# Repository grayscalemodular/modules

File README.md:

Technical documentation and source files for synthesizer modules developed by [Grayscale](https://grayscale.info/)

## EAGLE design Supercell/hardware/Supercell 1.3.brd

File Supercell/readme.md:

Supercell
=======

[Supercell](https://grayscale.info/supercell/) is a Eurorack synthesizer module from [Grayscale](https://grayscale.info/). It is primarily based on [Clouds](https://mutable-instruments.net/modules/clouds/) by [Mutable Instruments](https://mutable-instruments.net/). The original source files for Clouds can be found in the Mutable Instruments [Github](https://github.com/pichenettes/eurorack) repository.

Visit [grayscale.info/supercell/](https://grayscale.info/supercell/) for more information.

Hardware
=======

The schematic and PCB files for this project are distributed under the Creative Commons [CC-BY-SA 3.0](https://creativecommons.org/licenses/by-sa/3.0/) license, the same license used by the Clouds source files.

CC BY-SA license terms do not confer the right to use intellectual property such as trademarks, brand names, and logos. Grayscale, Microcell, Mutable Instruments, and Clouds are trademarks of their respective owners and should not be used without permission.

Firmware
=======

Supercell supports the Superparasites firmware, which combines elements of the original Clouds DSP code by [Mutable Instruments](https://github.com/pichenettes/eurorack), the [Parasites](https://mqtthiqs.github.io/parasites/clouds.html) alternate firmware by Matthias Puech, and the [Beat Repeat](https://github.com/jkammerl/eurorack) alternate firmware by Julius Kammerl. All source code is available on the [GitHub repo](https://github.com/patrickdowling/superparasites) maintained by Patrick Dowling. Thanks to all involved for their work on this hybrid code base.

Source code for this project is distributed under the MIT License. See [github.com/patrickdowling/superparasites](https://github.com/patrickdowling/superparasites) for source code.

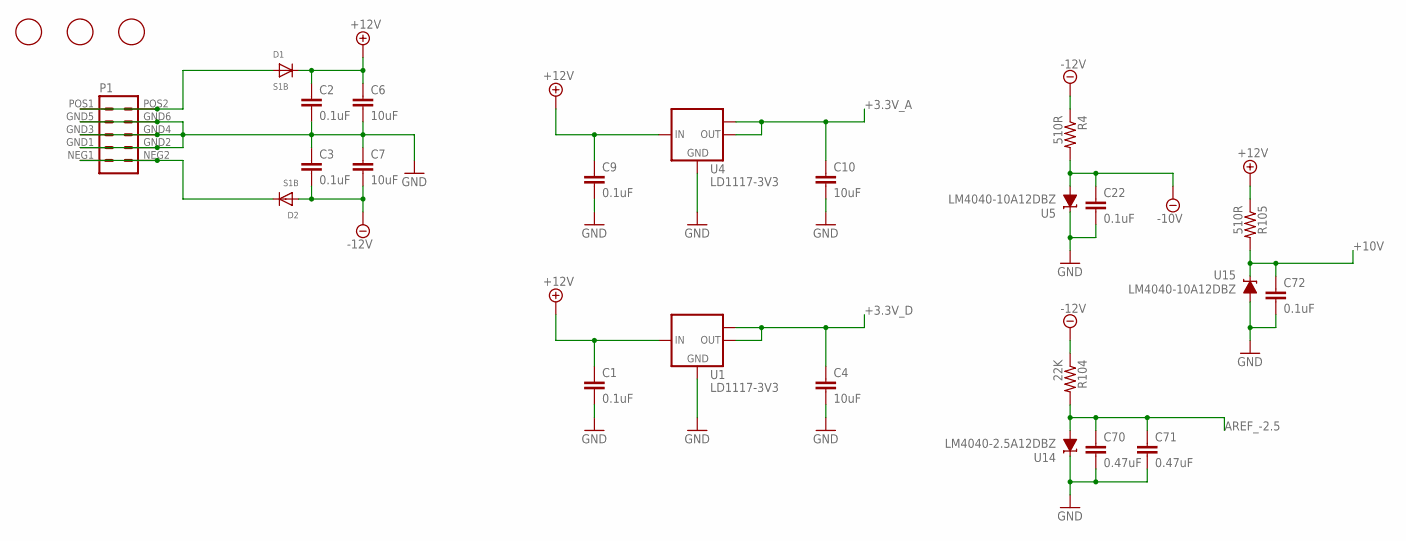
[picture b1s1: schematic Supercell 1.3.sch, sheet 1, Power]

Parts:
C1, C2, C3, C9, C22, C72: 0.1uF; C0603
C4, C6, C7, C10: 10uF; C0805
C70, C71: 0.47uF; C0603
D1, D2: S1B; SMADIODE
FD1, FD2, FD3: FIDUCIAL; FIDUCIAL_1MM
P1: EURO_POWER_HEADERLOCK_PADS; EURO_PWR_HEADER_LOCK
R4, R105: 510R; R0603
R104: 22K; R0603
U1, U4: LD1117-3V3; SOT223
U5, U15: LM4040-10A12DBZ; DBZ_R-PDSO-G3
U14: LM4040-2.5A12DBZ; DBZ_R-PDSO-G3

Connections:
+3.3V_A: C10.1, U4.2 (OUT), U4.TAB (OUT1); also elsewhere on the board
+3.3V_D: C4.1, U1.2 (OUT), U1.TAB (OUT1); also elsewhere on the board
+10V: C72.1, R105.2, U15.1 (C); also elsewhere on the board
+12V: C1.1, C2.1, C6.1, C9.1, D1.C, R105.1, U1.3 (IN), U4.3 (IN); also elsewhere on the board
-10V: C22.1, R4.2, U5.2 (A); also elsewhere on the board
-12V: C3.2, C7.2, D2.A, R4.1, R104.1; also elsewhere on the board
AREF_-2.5: C70.1, C71.1, R104.2, U14.2 (A); also elsewhere on the board
GND: C1.2, C2.2, C3.1, C4.2, C6.2, C7.1, C9.2, C10.2, C22.2, C70.2, C71.2, C72.2, P1.GND1 (4), P1.GND2 (3), P1.GND3 (6), P1.GND4 (5), P1.GND5 (8), P1.GND6 (7), U1.1 (GND), U4.1 (GND), U5.1 (C), U14.1 (C), U15.2 (A); also elsewhere on the board
unnamed: D1.A, P1.POS1 (10), P1.POS2 (9)
unnamed: D2.C, P1.NEG1 (2), P1.NEG2 (1)

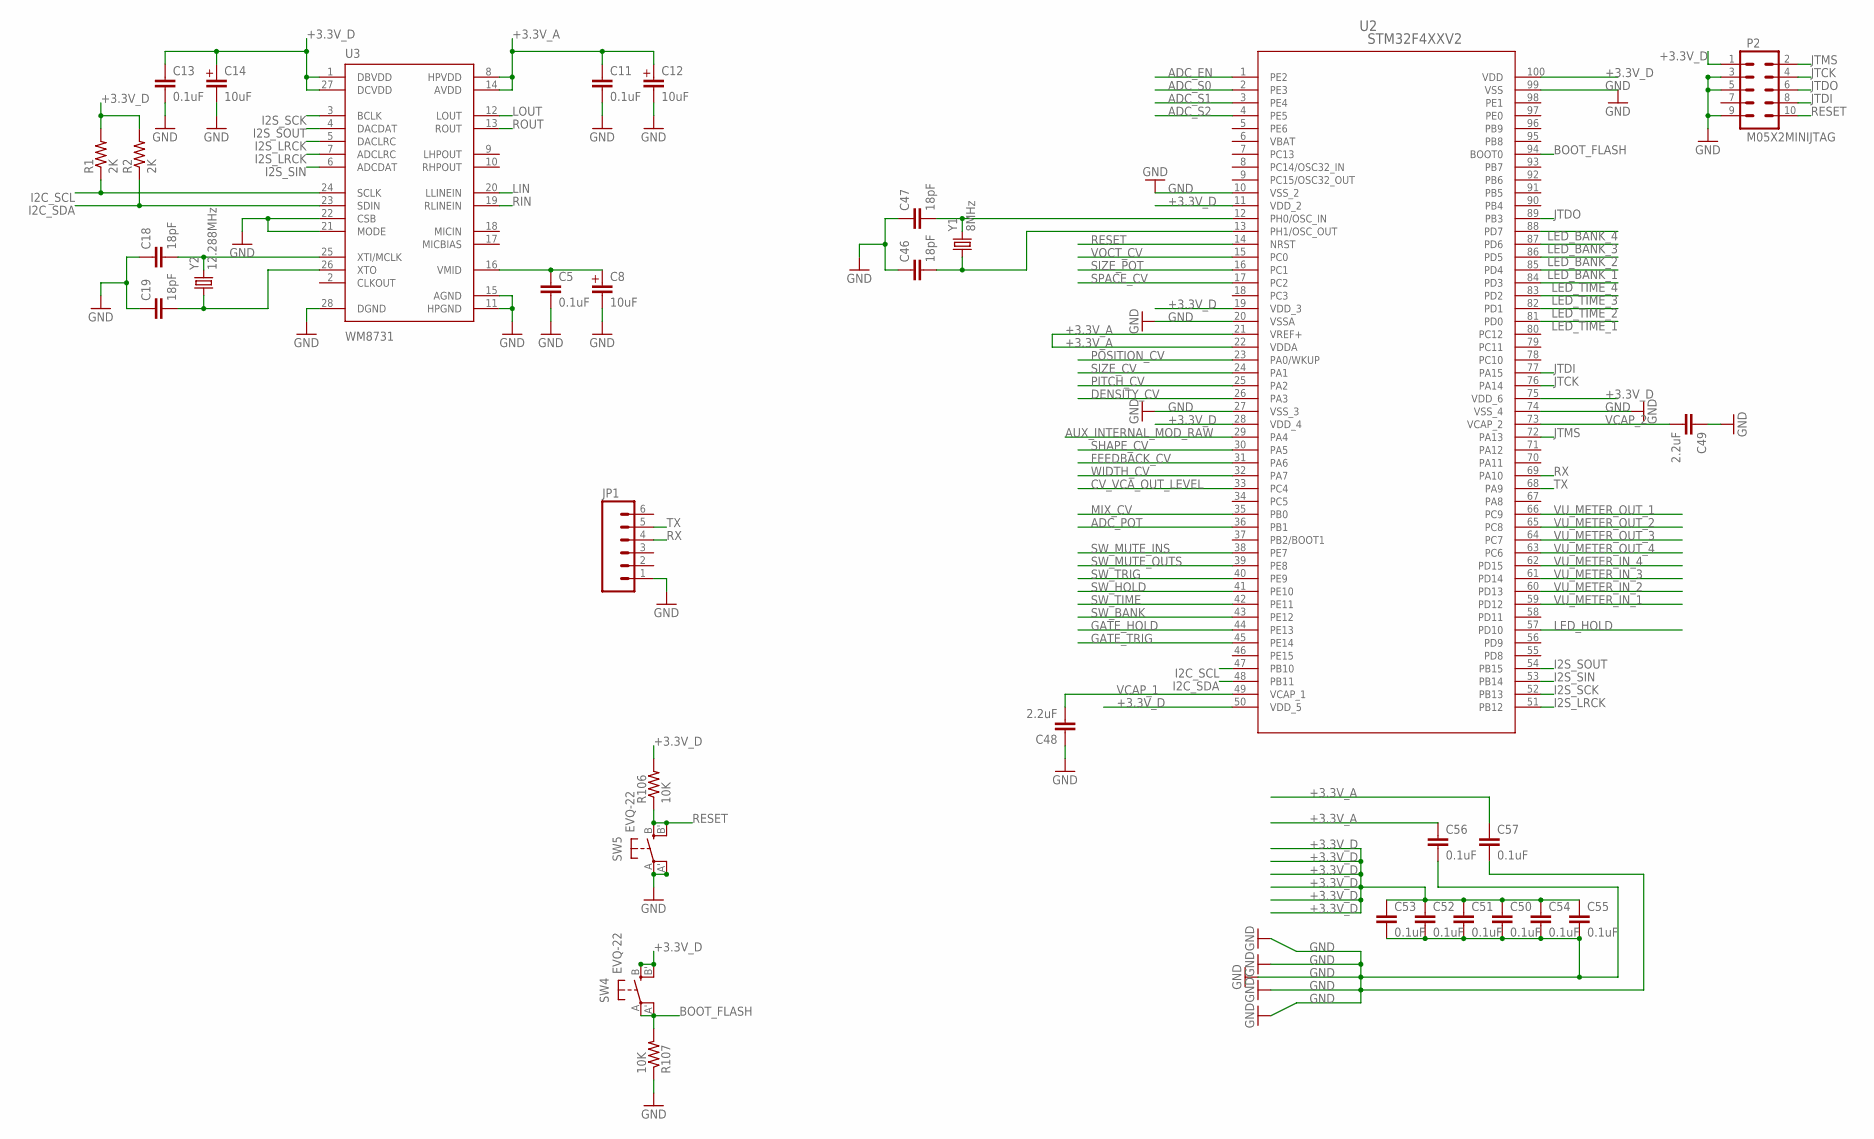
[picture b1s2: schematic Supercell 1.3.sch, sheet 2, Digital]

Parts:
C5, C11, C13, C50, C51, C52, C53, C54, C55, C56, C57: 0.1uF; C0603
C8, C12, C14: 10uF; EC-4X7
C18, C19, C46, C47: 18pF; C0603
C48, C49: 2.2uF; C0603
JP1: M06SIP; 1X06
P2: M05X2MINIJTAG; 2X5-1.27
R1, R2: 2K; R0603
R106, R107: 10K; R0603
SW4, SW5: EVQ-22; EVQ-Q2
U2: STM32F4XXV2; LQFP100-14X14MM
U3: WM8731; SSOP28
Y1: 8MHz; HC49UP
Y2: 12.288MHz; HC49UP

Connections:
+3.3V_A: C11.1, C12.P$1 (POS), C56.1, C57.1, U2.21 (VREF+), U2.22 (VDDA), U3.8 (HPVDD), U3.14 (AVDD); also elsewhere on the board
+3.3V_D: C13.1, C14.P$1 (POS), C50.1, C51.1, C52.1, C53.1, C54.1, C55.1, P2.1, R1.2, R2.2, R106.2, SW4.B (S), SW4.B' (S1), U2.11 (VDD_2), U2.19 (VDD_3), U2.28 (VDD_4), U2.50 (VDD_5), U2.75 (VDD_6), U2.100 (VDD), U3.1 (DBVDD), U3.27 (DCVDD); also elsewhere on the board
ADC_EN: U2.1 (PE2); also elsewhere on the board
ADC_POT: U2.36 (PB1); also elsewhere on the board
ADC_S0: U2.2 (PE3); also elsewhere on the board
ADC_S1: U2.3 (PE4); also elsewhere on the board
ADC_S2: U2.4 (PE5); also elsewhere on the board
AUX_INTERNAL_MOD_RAW: U2.29 (PA4); also elsewhere on the board
BOOT_FLASH: R107.2, SW4.A, SW4.A' (P1), U2.94 (BOOT0)
CV_VCA_OUT_LEVEL: U2.33 (PC4); also elsewhere on the board
DENSITY_CV: U2.26 (PA3); also elsewhere on the board
FEEDBACK_CV: U2.31 (PA6); also elsewhere on the board
GATE_HOLD: U2.44 (PE13); also elsewhere on the board
GATE_TRIG: U2.45 (PE14); also elsewhere on the board
GND: C5.2, C8.P$2 (NEG), C11.2, C12.P$2 (NEG), C13.2, C14.P$2 (NEG), C18.1, C19.1, C46.1, C47.1, C48.1, C49.1, C50.2, C51.2, C52.2, C53.2, C54.2, C55.2, C56.2, C57.2, JP1.1, P2.3, P2.5, P2.9, R107.1, SW5.A, SW5.A' (P1), U2.10 (VSS_2), U2.20 (VSSA), U2.27 (VSS_3), U2.74 (VSS_4), U2.99 (VSS), U3.11 (HPGND), U3.15 (AGND), U3.21 (MODE), U3.22 (CSB), U3.28 (DGND); also elsewhere on the board
I2C_SCL: R1.1, U2.47 (PB10), U3.24 (SCLK)
I2C_SDA: R2.1, U2.48 (PB11), U3.23 (SDIN)
I2S_LRCK: U2.51 (PB12), U3.5 (DACLRC), U3.7 (ADCLRC)
I2S_SCK: U2.52 (PB13), U3.3 (BCLK)
I2S_SIN: U2.53 (PB14), U3.6 (ADCDAT)
I2S_SOUT: U2.54 (PB15), U3.4 (DACDAT)
JTCK: P2.4, U2.76 (PA14)
JTDI: P2.8, U2.77 (PA15)
JTDO: P2.6, U2.89 (PB3)
JTMS: P2.2, U2.72 (PA13)
LED_BANK_1: U2.85 (PD4); also elsewhere on the board
LED_BANK_2: U2.86 (PD5); also elsewhere on the board
LED_BANK_3: U2.87 (PD6); also elsewhere on the board
LED_BANK_4: U2.88 (PD7); also elsewhere on the board
LED_HOLD: U2.57 (PD10); also elsewhere on the board
LED_TIME_1: U2.81 (PD0); also elsewhere on the board
LED_TIME_2: U2.82 (PD1); also elsewhere on the board
LED_TIME_3: U2.83 (PD2); also elsewhere on the board
LED_TIME_4: U2.84 (PD3); also elsewhere on the board
LIN: U3.20 (LLINEIN); also elsewhere on the board
LOUT: U3.12 (LOUT); also elsewhere on the board
MIX_CV: U2.35 (PB0); also elsewhere on the board
unnamed: C5.1, C8.P$1 (POS), U3.16 (VMID)
unnamed: C19.2, U3.26 (XTO), Y2.1
unnamed: C18.2, U3.25 (XTI/MCLK), Y2.2
unnamed: C46.2, U2.13 (PH1/OSC_OUT), Y1.1
unnamed: C47.2, U2.12 (PH0/OSC_IN), Y1.2
PITCH_CV: U2.25 (PA2); also elsewhere on the board
POSITION_CV: U2.23 (PA0/WKUP); also elsewhere on the board
RESET: P2.10, R106.1, SW5.B (S), SW5.B' (S1), U2.14 (NRST)
RIN: U3.19 (RLINEIN); also elsewhere on the board
ROUT: U3.13 (ROUT); also elsewhere on the board
RX: JP1.4, U2.69 (PA10)
SHAPE_CV: U2.30 (PA5); also elsewhere on the board
SIZE_CV: U2.24 (PA1); also elsewhere on the board
SIZE_POT: U2.16 (PC1); also elsewhere on the board
SPACE_CV: U2.17 (PC2); also elsewhere on the board
SW_BANK: U2.43 (PE12); also elsewhere on the board
SW_HOLD: U2.41 (PE10); also elsewhere on the board
SW_MUTE_INS: U2.38 (PE7); also elsewhere on the board
SW_MUTE_OUTS: U2.39 (PE8); also elsewhere on the board
SW_TIME: U2.42 (PE11); also elsewhere on the board
SW_TRIG: U2.40 (PE9); also elsewhere on the board
TX: JP1.5, U2.68 (PA9)
VBAT: U2.6 (VBAT)
VCAP_1: C48.2, U2.49 (VCAP_1)
VCAP_2: C49.2, U2.73 (VCAP_2)
VOCT_CV: U2.15 (PC0); also elsewhere on the board
VU_METER_IN_1: U2.59 (PD12); also elsewhere on the board
VU_METER_IN_2: U2.60 (PD13); also elsewhere on the board
VU_METER_IN_3: U2.61 (PD14); also elsewhere on the board
VU_METER_IN_4: U2.62 (PD15); also elsewhere on the board
VU_METER_OUT_1: U2.66 (PC9); also elsewhere on the board
VU_METER_OUT_2: U2.65 (PC8); also elsewhere on the board
VU_METER_OUT_3: U2.64 (PC7); also elsewhere on the board
VU_METER_OUT_4: U2.63 (PC6); also elsewhere on the board
WIDTH_CV: U2.32 (PA7); also elsewhere on the board

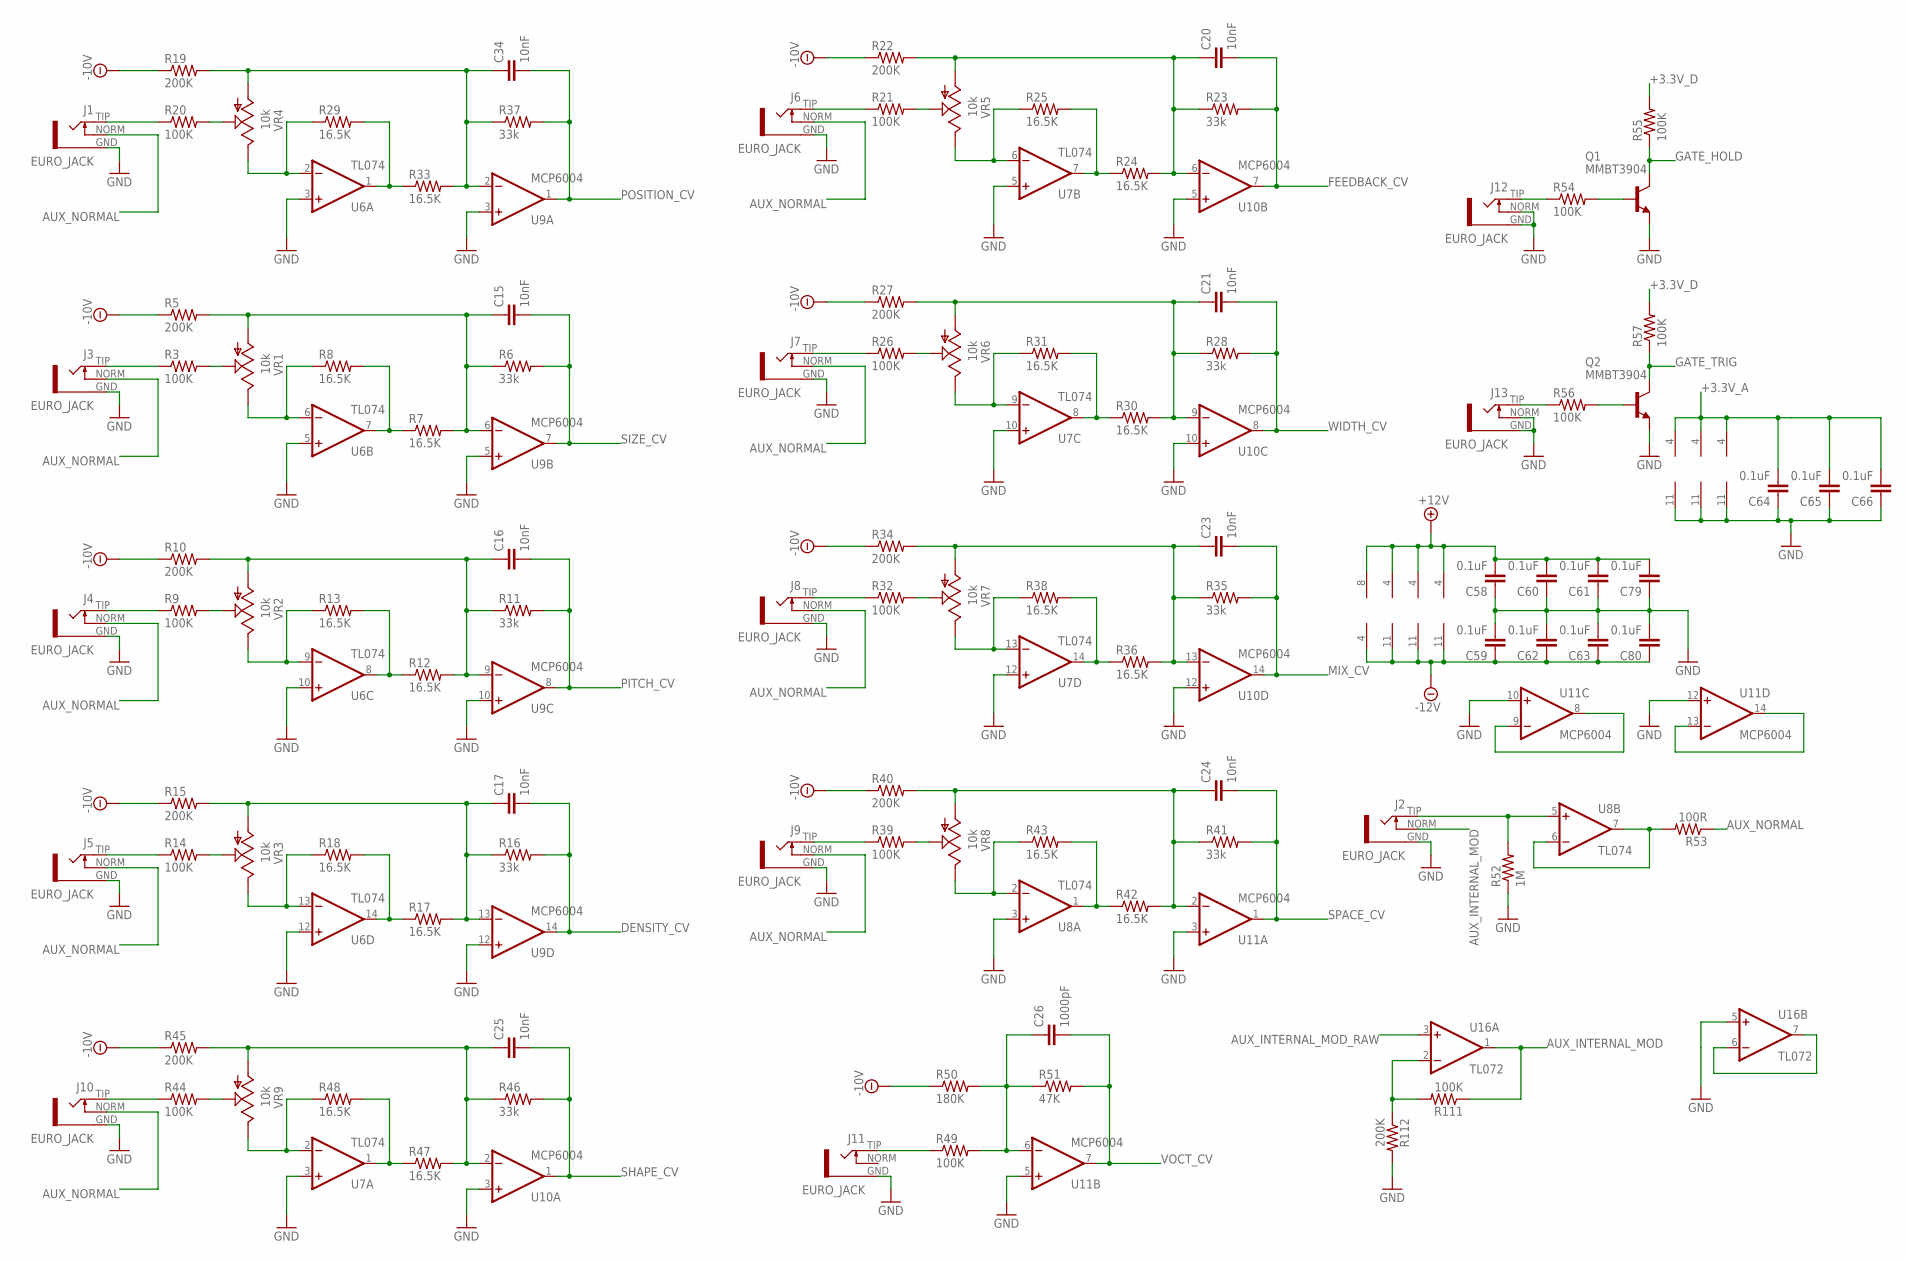
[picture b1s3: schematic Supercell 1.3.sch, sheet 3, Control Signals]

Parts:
C15, C16, C17, C20, C21, C23, C24, C25, C34: 10nF; C0603
C26: 1000pF; C0603
C58, C59, C60, C61, C62, C63, C64, C65, C66, C79, C80: 0.1uF; C0603
J1, J2, J3, J4, J5, J6, J7, J8, J9, J10, J11, J12, J13: EURO_JACK; S_JACK
Q1, Q2: MMBT3904; SOT23-BEC
R3, R9, R14, R20, R21, R26, R32, R39, R44, R49, R54, R55, R56, R57, R111: 100K; R0603
R5, R10, R15, R19, R22, R27, R34, R40, R45, R112: 200K; R0603
R6, R11, R16, R23, R28, R35, R37, R41, R46: 33k; R0603
R7, R8, R12, R13, R17, R18, R24, R25, R29, R30, R31, R33, R36, R38, R42, R43, R47, R48: 16.5K; R0603
R50: 180K; R0603
R51: 47K; R0603
R52: 1M; R0603
R53: 100R; R0603
U6, U7, U8: TL074; SO14
U9, U10, U11: MCP6004; SO14
U16: TL072; SO08_BOXPIN
VR1, VR2, VR3, VR4, VR5, VR6, VR7, VR8, VR9: 10k; 9MM_SNAP-IN_POT_NO_SILK

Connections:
+3.3V_A: C64.2, C65.2, C66.2, U9.4 (V+), U10.4 (V+), U11.4 (V+); also elsewhere on the board
+3.3V_D: R55.2, R57.2; also elsewhere on the board
+12V: C58.2, C60.2, C61.2, C79.2, U6.4 (V+), U7.4 (V+), U8.4 (V+), U16.8 (V+); also elsewhere on the board
-10V: R5.1, R10.1, R15.1, R19.1, R22.1, R27.1, R34.1, R40.1, R45.1, R50.1; also elsewhere on the board
-12V: C59.1, C62.1, C63.1, C80.1, U6.11 (V-), U7.11 (V-), U8.11 (V-), U16.4 (V-); also elsewhere on the board
AUX_INTERNAL_MOD: J2.NORM, R111.1, U16.1 (OUT)
AUX_INTERNAL_MOD_RAW: U16.3 (+IN); also elsewhere on the board
AUX_NORMAL: J1.NORM, J3.NORM, J4.NORM, J5.NORM, J6.NORM, J7.NORM, J8.NORM, J9.NORM, J10.NORM, R53.1
DENSITY_CV: C17.2, R16.2, U9.14 (OUT); also elsewhere on the board
FEEDBACK_CV: C20.2, R23.2, U10.7 (OUT); also elsewhere on the board
GATE_HOLD: Q1.C, R55.1; also elsewhere on the board
GATE_TRIG: Q2.C, R57.1; also elsewhere on the board
GND: C58.1, C59.2, C60.1, C61.1, C62.2, C63.2, C64.1, C65.1, C66.1, C79.1, C80.2, J1.GND, J2.GND, J3.GND, J4.GND, J5.GND, J6.GND, J7.GND, J8.GND, J9.GND, J10.GND, J11.GND, J12.GND, J12.NORM, J13.GND, J13.NORM, Q1.E, Q2.E, R52.1, R112.2, U6.3 (+IN), U6.5 (+IN), U6.10 (+IN), U6.12 (+IN), U7.3 (+IN), U7.5 (+IN), U7.10 (+IN), U7.12 (+IN), U8.3 (+IN), U9.3 (+IN), U9.5 (+IN), U9.10 (+IN), U9.11 (V-), U9.12 (+IN), U10.3 (+IN), U10.5 (+IN), U10.10 (+IN), U10.11 (V-), U10.12 (+IN), U11.3 (+IN), U11.5 (+IN), U11.10 (+IN), U11.11 (V-), U11.12 (+IN), U16.5 (+IN); also elsewhere on the board
MIX_CV: C23.2, R35.2, U10.14 (OUT); also elsewhere on the board
unnamed: J2.TIP, R52.2, U8.5 (+IN)
unnamed: J3.TIP, R3.1
unnamed: C15.1, R5.2, R6.1, R7.2, U9.6 (-IN), VR1.1
unnamed: R8.1, U6.6 (-IN), VR1.3
unnamed: R7.1, R8.2, U6.7 (OUT)
unnamed: R3.2, VR1.2
unnamed: J4.TIP, R9.1
unnamed: C16.1, R10.2, R11.1, R12.2, U9.9 (-IN), VR2.1
unnamed: R13.1, U6.9 (-IN), VR2.3
unnamed: R12.1, R13.2, U6.8 (OUT)
unnamed: R9.2, VR2.2
unnamed: J5.TIP, R14.1
unnamed: C17.1, R15.2, R16.1, R17.2, U9.13 (-IN), VR3.1
unnamed: R18.1, U6.13 (-IN), VR3.3
unnamed: R17.1, R18.2, U6.14 (OUT)
unnamed: R14.2, VR3.2
unnamed: J6.TIP, R21.1
unnamed: C20.1, R22.2, R23.1, R24.2, U10.6 (-IN), VR5.1
unnamed: R25.1, U7.6 (-IN), VR5.3
unnamed: R24.1, R25.2, U7.7 (OUT)
unnamed: R21.2, VR5.2
unnamed: J7.TIP, R26.1
unnamed: C21.1, R27.2, R28.1, R30.2, U10.9 (-IN), VR6.1
unnamed: R31.1, U7.9 (-IN), VR6.3
unnamed: R30.1, R31.2, U7.8 (OUT)
unnamed: R26.2, VR6.2
unnamed: J8.TIP, R32.1
unnamed: C23.1, R34.2, R35.1, R36.2, U10.13 (-IN), VR7.1
unnamed: R38.1, U7.13 (-IN), VR7.3
unnamed: R36.1, R38.2, U7.14 (OUT)
unnamed: R32.2, VR7.2
unnamed: J9.TIP, R39.1
unnamed: C24.1, R40.2, R41.1, R42.2, U11.2 (-IN), VR8.1
unnamed: R43.1, U8.2 (-IN), VR8.3
unnamed: R42.1, R43.2, U8.1 (OUT)
unnamed: R39.2, VR8.2
unnamed: J10.TIP, R44.1
unnamed: C25.1, R45.2, R46.1, R47.2, U10.2 (-IN), VR9.1
unnamed: R48.1, U7.2 (-IN), VR9.3
unnamed: R47.1, R48.2, U7.1 (OUT)
unnamed: R44.2, VR9.2
unnamed: J11.TIP, R49.1
unnamed: R53.2, U8.6 (-IN), U8.7 (OUT)
unnamed: Q1.B, R54.2
unnamed: J12.TIP, R54.1
unnamed: C26.1, R49.2, R50.2, R51.1, U11.6 (-IN)
unnamed: Q2.B, R56.2
unnamed: J13.TIP, R56.1
unnamed: J1.TIP, R20.1
unnamed: C34.1, R19.2, R33.2, R37.1, U9.2 (-IN), VR4.1
unnamed: R29.1, U6.2 (-IN), VR4.3
unnamed: R29.2, R33.1, U6.1 (OUT)
unnamed: R20.2, VR4.2
unnamed: U11.8 (OUT), U11.9 (-IN)
unnamed: U11.13 (-IN), U11.14 (OUT)
unnamed: R111.2, R112.1, U16.2 (-IN)
unnamed: U16.6 (-IN), U16.7 (OUT)
PITCH_CV: C16.2, R11.2, U9.8 (OUT); also elsewhere on the board
POSITION_CV: C34.2, R37.2, U9.1 (OUT); also elsewhere on the board
SHAPE_CV: C25.2, R46.2, U10.1 (OUT); also elsewhere on the board
SIZE_CV: C15.2, R6.2, U9.7 (OUT); also elsewhere on the board
SPACE_CV: C24.2, R41.2, U11.1 (OUT); also elsewhere on the board
VOCT_CV: C26.2, R51.2, U11.7 (OUT); also elsewhere on the board
WIDTH_CV: C21.2, R28.2, U10.8 (OUT); also elsewhere on the board

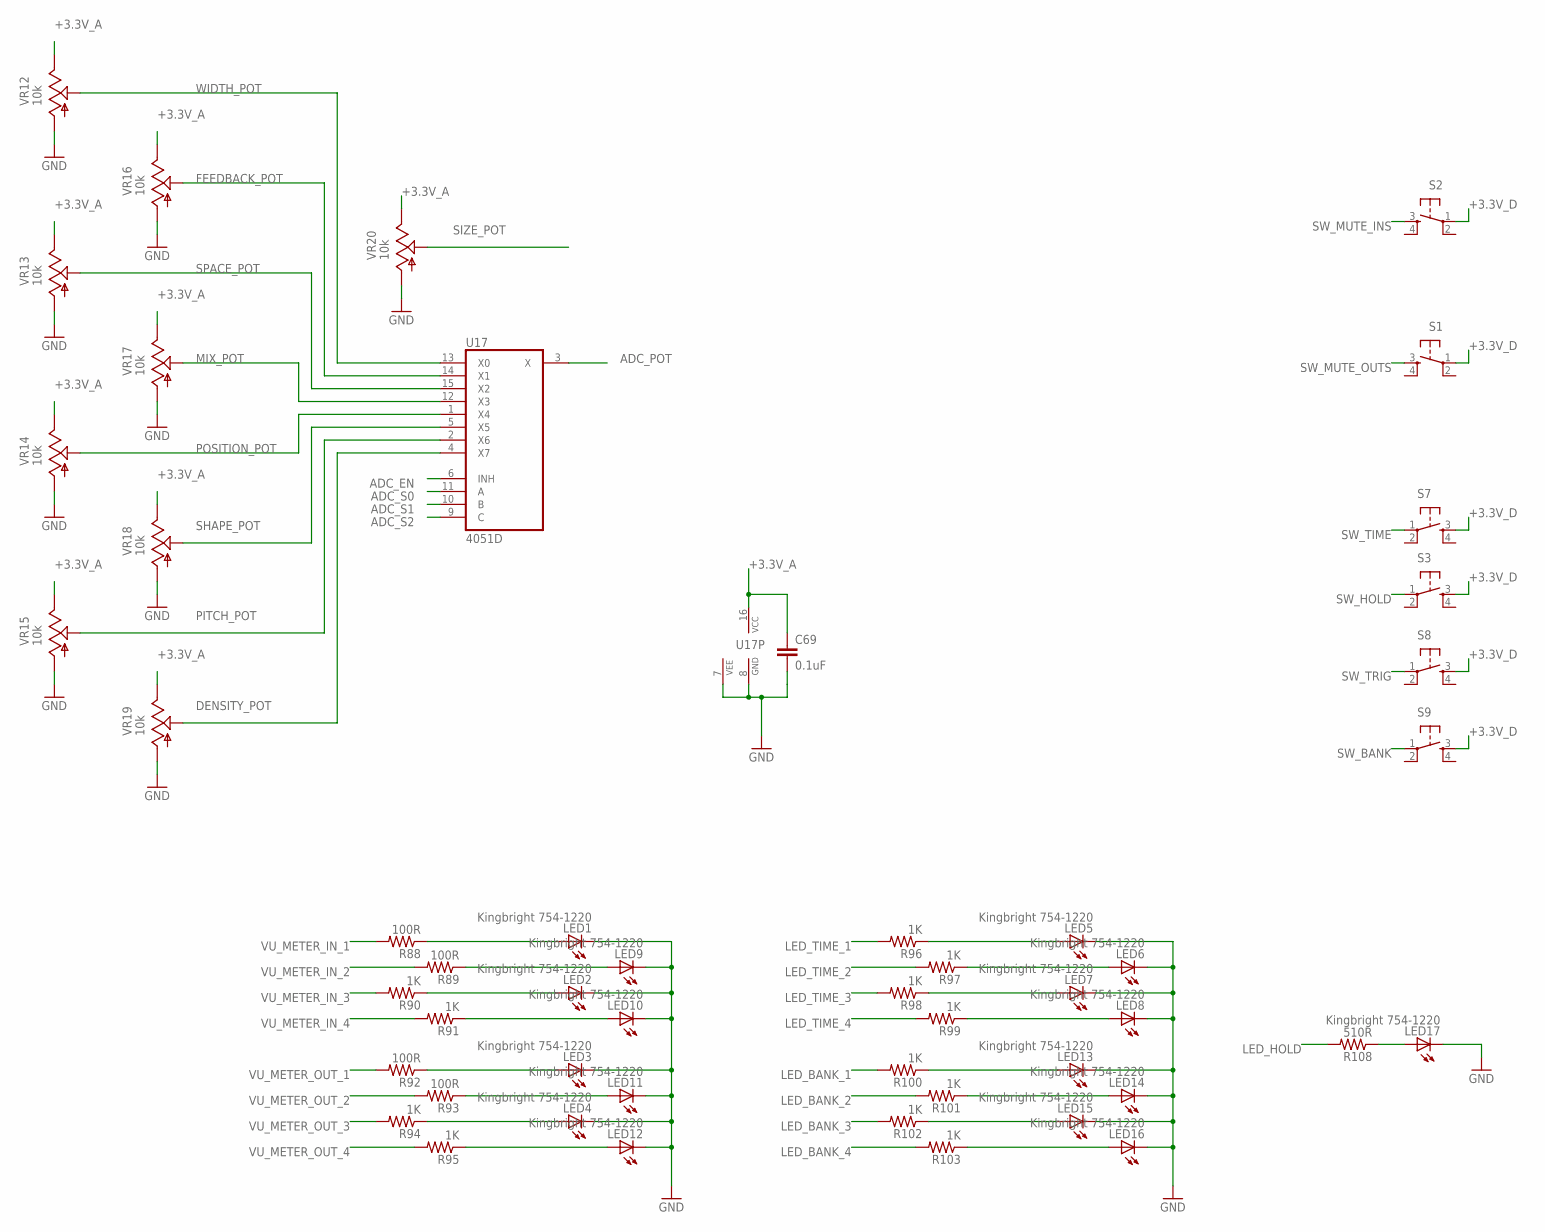
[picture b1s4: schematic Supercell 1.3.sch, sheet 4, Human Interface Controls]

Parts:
C69: 0.1uF; C0603
LED1, LED2, LED3, LED4, LED5, LED6, LED7, LED8, LED9, LED10, LED11, LED12, LED13, LED14, LED15, LED16, LED17: Kingbright 754-1220; LED_3MM_MIN
R88, R89, R92, R93: 100R; R0603
R90, R91, R94, R95, R96, R97, R98, R99, R100, R101, R102, R103: 1K; R0603
R108: 510R; R0603
S1, S2: TAC_SWITCHPTH; TACTILE-PTH
S3, S7, S8, S9: TAC_SWITCH; C&K_D6R
U17: 4051D; SO16
VR12, VR13, VR14, VR15, VR16, VR17, VR18, VR19, VR20: 10k; 9MM_SNAP-IN_POT_NO_SILK

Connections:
+3.3V_A: C69.1, U17.16 (VCC), VR12.3, VR13.3, VR14.3, VR15.3, VR16.3, VR17.3, VR18.3, VR19.3, VR20.3; also elsewhere on the board
+3.3V_D: S1.1, S2.1, S3.3, S7.3, S8.3, S9.3; also elsewhere on the board
ADC_EN: U17.6 (INH); also elsewhere on the board
ADC_POT: U17.3 (X); also elsewhere on the board
ADC_S0: U17.11 (A); also elsewhere on the board
ADC_S1: U17.10 (B); also elsewhere on the board
ADC_S2: U17.9 (C); also elsewhere on the board
DENSITY_POT: U17.4 (X7), VR19.2
FEEDBACK_POT: U17.14 (X1), VR16.2
GND: C69.2, LED1.K (C), LED2.K (C), LED3.K (C), LED4.K (C), LED5.K (C), LED6.K (C), LED7.K (C), LED8.K (C), LED9.K (C), LED10.K (C), LED11.K (C), LED12.K (C), LED13.K (C), LED14.K (C), LED15.K (C), LED16.K (C), LED17.K (C), U17.7 (VEE), U17.8 (GND), VR12.1, VR13.1, VR14.1, VR15.1, VR16.1, VR17.1, VR18.1, VR19.1, VR20.1; also elsewhere on the board
LED_BANK_1: R100.2; also elsewhere on the board
LED_BANK_2: R101.2; also elsewhere on the board
LED_BANK_3: R102.2; also elsewhere on the board
LED_BANK_4: R103.2; also elsewhere on the board
LED_HOLD: R108.2; also elsewhere on the board
LED_TIME_1: R96.2; also elsewhere on the board
LED_TIME_2: R97.2; also elsewhere on the board
LED_TIME_3: R98.2; also elsewhere on the board
LED_TIME_4: R99.2; also elsewhere on the board
MIX_POT: U17.12 (X3), VR17.2
unnamed: LED9.A, R89.1
unnamed: LED17.A, R108.1
unnamed: LED1.A, R88.1
unnamed: LED2.A, R90.1
unnamed: LED10.A, R91.1
unnamed: LED3.A, R92.1
unnamed: LED11.A, R93.1
unnamed: LED4.A, R94.1
unnamed: LED12.A, R95.1
unnamed: LED6.A, R97.1
unnamed: LED5.A, R96.1
unnamed: LED7.A, R98.1
unnamed: LED8.A, R99.1
unnamed: LED13.A, R100.1
unnamed: LED14.A, R101.1
unnamed: LED15.A, R102.1
unnamed: LED16.A, R103.1
PITCH_POT: U17.2 (X6), VR15.2
POSITION_POT: U17.1 (X4), VR14.2
SHAPE_POT: U17.5 (X5), VR18.2
SIZE_POT: VR20.2; also elsewhere on the board
SPACE_POT: U17.15 (X2), VR13.2
SW_BANK: S9.1; also elsewhere on the board
SW_HOLD: S3.1; also elsewhere on the board
SW_MUTE_INS: S2.3; also elsewhere on the board
SW_MUTE_OUTS: S1.3; also elsewhere on the board
SW_TIME: S7.1; also elsewhere on the board
SW_TRIG: S8.1; also elsewhere on the board
VU_METER_IN_1: R88.2; also elsewhere on the board
VU_METER_IN_2: R89.2; also elsewhere on the board
VU_METER_IN_3: R90.2; also elsewhere on the board
VU_METER_IN_4: R91.2; also elsewhere on the board
VU_METER_OUT_1: R92.2; also elsewhere on the board
VU_METER_OUT_2: R93.2; also elsewhere on the board
VU_METER_OUT_3: R94.2; also elsewhere on the board
VU_METER_OUT_4: R95.2; also elsewhere on the board
WIDTH_POT: U17.13 (X0), VR12.2

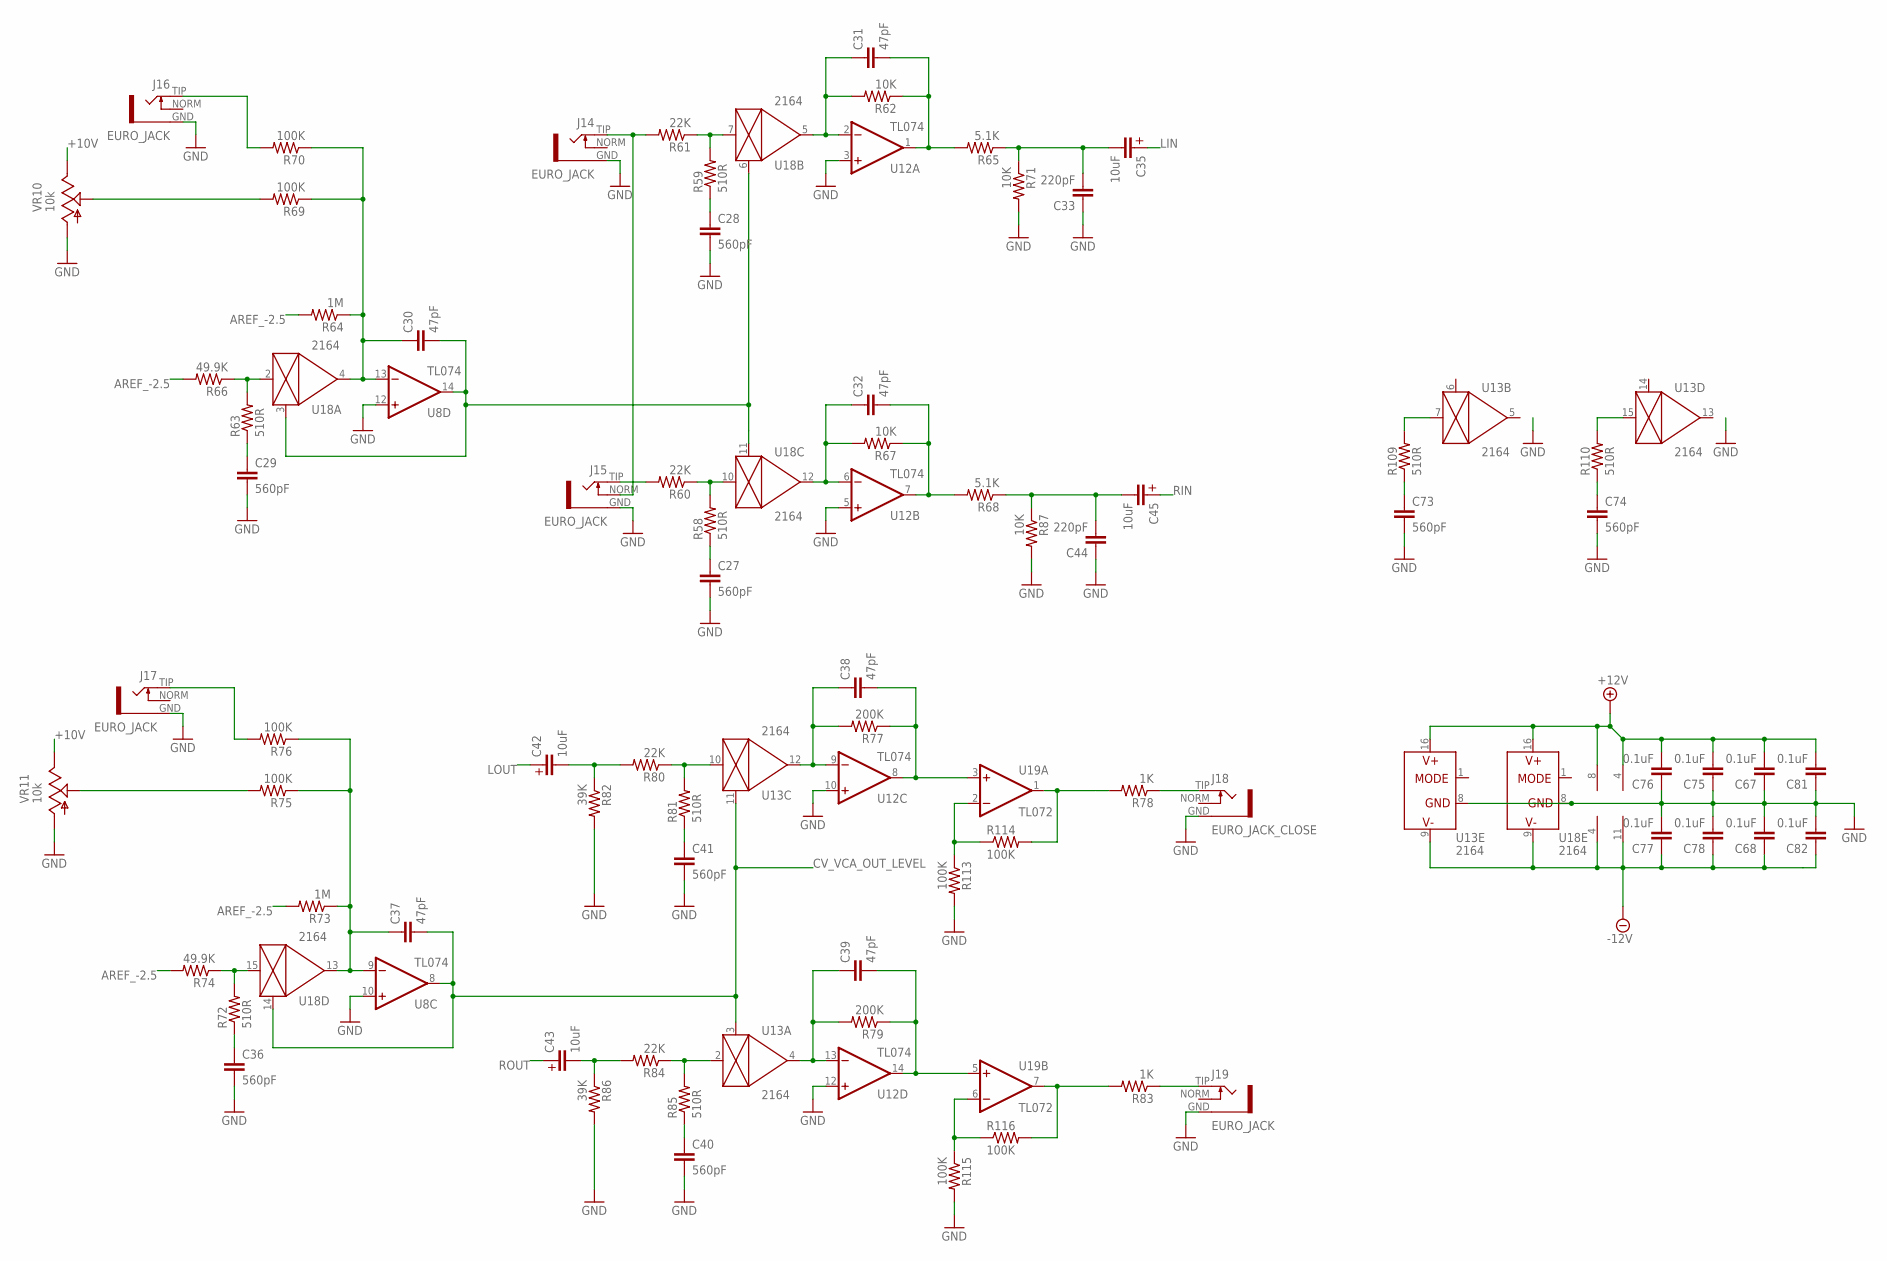
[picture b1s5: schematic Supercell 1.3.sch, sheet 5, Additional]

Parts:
C27, C28, C29, C36, C40, C41, C73, C74: 560pF; C0603
C30, C31, C32, C37, C38, C39: 47pF; C0603
C33, C44: 220pF; C0603
C35, C42, C43, C45: 10uF; EC-4X7
C67, C68, C75, C76, C77, C78, C81, C82: 0.1uF; C0603
J14, J15, J16, J17, J19: EURO_JACK; S_JACK
J18: EURO_JACK_CLOSE; S_JACK_CLOSE
R58, R59, R63, R72, R81, R85, R109, R110: 510R; R0603
R60, R61, R80, R84: 22K; R0603
R62, R67, R71, R87: 10K; R0603
R64, R73: 1M; R0603
R65, R68: 5.1K; R0603
R66, R74: 49.9K; R0603
R69, R70, R75, R76, R113, R114, R115, R116: 100K; R0603
R77, R79: 200K; R0603
R78, R83: 1K; R0603
R82, R86: 39K; R0603
U8, U12: TL074; SO14
U13, U18: 2164; SO16
U19: TL072; SO08_BOXPIN
VR10, VR11: 10k; 9MM_SNAP-IN_POT_NO_SILK

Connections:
+10V: VR10.3, VR11.3; also elsewhere on the board
+12V: C67.2, C75.2, C76.2, C81.2, U12.4 (V+), U13.16 (V+), U18.16 (V+), U19.8 (V+); also elsewhere on the board
-12V: C68.1, C77.1, C78.1, C82.1, U12.11 (V-), U13.9 (V-), U18.9 (V-), U19.4 (V-); also elsewhere on the board
AREF_-2.5: R64.2, R66.2, R73.2, R74.2; also elsewhere on the board
CV_VCA_OUT_LEVEL: C37.2, U8.8 (OUT), U13.3 (CTRL), U13.11 (CTRL), U18.14 (CTRL); also elsewhere on the board
GND: C27.2, C28.2, C29.2, C33.1, C36.2, C40.2, C41.2, C44.1, C67.1, C68.2, C73.2, C74.2, C75.1, C76.1, C77.2, C78.2, C81.1, C82.2, J14.GND, J15.GND, J16.GND, J17.GND, J18.GND, J19.GND, R71.2, R82.2, R86.2, R87.2, R113.2, R115.2, U8.10 (+IN), U8.12 (+IN), U12.3 (+IN), U12.5 (+IN), U12.10 (+IN), U12.12 (+IN), U13.8 (GND), U18.8 (GND), VR10.1, VR11.1; also elsewhere on the board
LIN: C35.P$1 (POS); also elsewhere on the board
LOUT: C42.P$1 (POS); also elsewhere on the board
unnamed: C28.1, R59.1
unnamed: C27.1, R58.1
unnamed: C29.1, R63.1
unnamed: C30.2, U8.14 (OUT), U18.3 (CTRL), U18.6 (CTRL), U18.11 (CTRL)
unnamed: R58.2, R60.1, U18.10 (IN)
unnamed: R63.2, R66.1, U18.2 (IN)
unnamed: C32.1, R67.2, U12.6 (-IN), U18.12 (OUT)
unnamed: C32.2, R67.1, R68.2, U12.7 (OUT)
unnamed: J14.TIP, J15.NORM, R61.2
unnamed: J15.TIP, R60.2
unnamed: J16.TIP, R70.2
unnamed: C36.1, R72.1
unnamed: R69.2, VR10.2
unnamed: R72.2, R74.1, U18.15 (IN)
unnamed: J17.TIP, R76.2
unnamed: R75.2, VR11.2
unnamed: C38.1, R77.2, U12.9 (-IN), U13.12 (OUT)
unnamed: C38.2, R77.1, U12.8 (OUT), U19.3 (+IN)
unnamed: R59.2, R61.1, U18.7 (IN)
unnamed: R109.2, U13.7 (IN)
unnamed: J18.TIP, R78.1
unnamed: R80.1, R81.2, U13.10 (IN)
unnamed: C41.1, R81.1
unnamed: C42.P$2 (NEG), R80.2, R82.1
unnamed: C44.2, C45.P$2 (NEG), R68.1, R87.1
unnamed: C39.1, R79.2, U12.13 (-IN), U13.4 (OUT)
unnamed: C39.2, R79.1, U12.14 (OUT), U19.5 (+IN)
unnamed: R84.1, R85.2, U13.2 (IN)
unnamed: C40.1, R85.1
unnamed: C43.P$2 (NEG), R84.2, R86.1
unnamed: R110.2, U13.15 (IN)
unnamed: J19.TIP, R83.1
unnamed: C31.1, R62.2, U12.2 (-IN), U18.5 (OUT)
unnamed: C31.2, R62.1, R65.2, U12.1 (OUT)
unnamed: R113.1, R114.1, U19.2 (-IN)
unnamed: C73.1, R109.1
unnamed: C74.1, R110.1
unnamed: R78.2, R114.2, U19.1 (OUT)
unnamed: R115.1, R116.1, U19.6 (-IN)
unnamed: R83.2, R116.2, U19.7 (OUT)
unnamed: C33.2, C35.P$2 (NEG), R65.1, R71.1
RIN: C45.P$1 (POS); also elsewhere on the board
ROUT: C43.P$1 (POS); also elsewhere on the board
VCA_CTRL_INPUTS: C30.1, R64.1, R69.1, R70.1, U8.13 (-IN), U18.4 (OUT)
VCA_CTRL_INPUTS1: C37.1, R73.1, R75.1, R76.1, U8.9 (-IN), U18.13 (OUT)

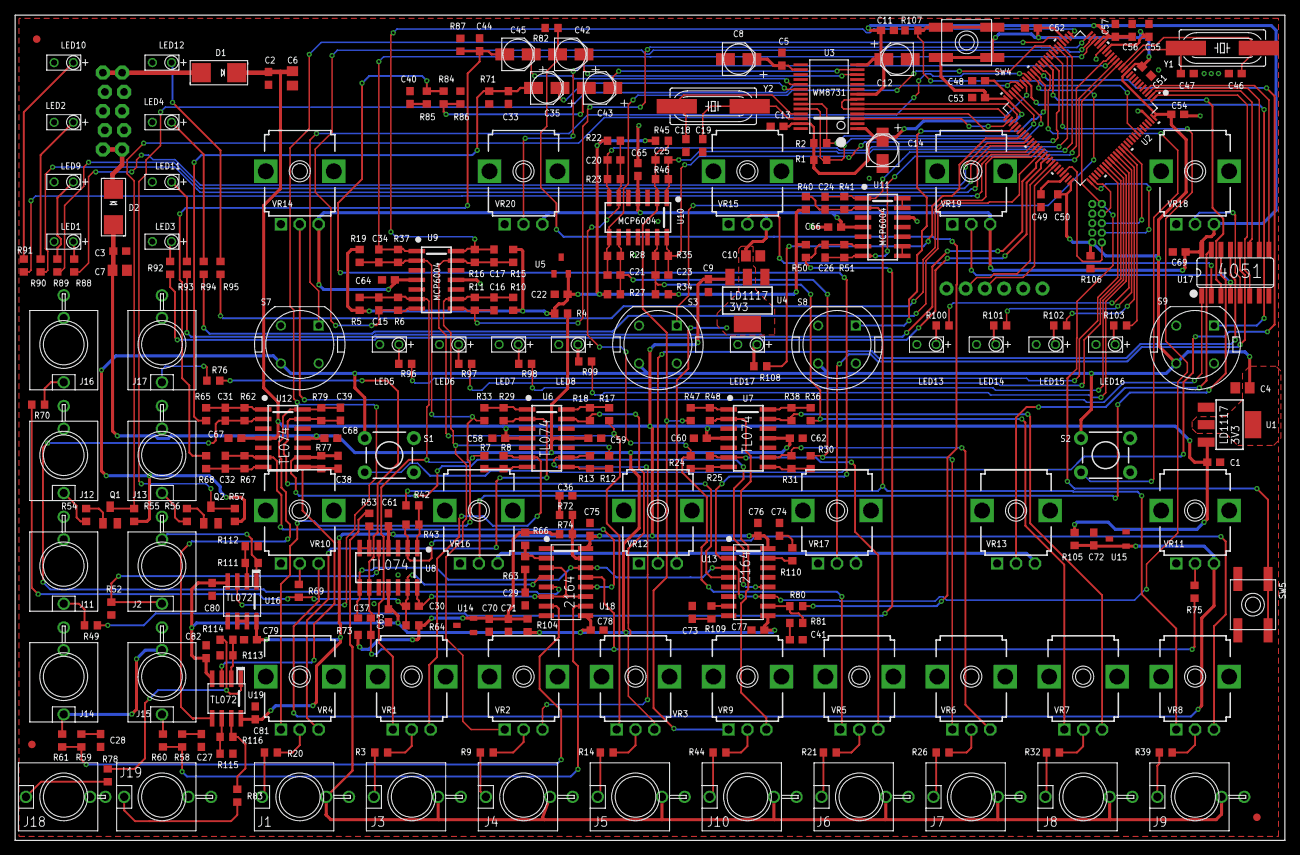
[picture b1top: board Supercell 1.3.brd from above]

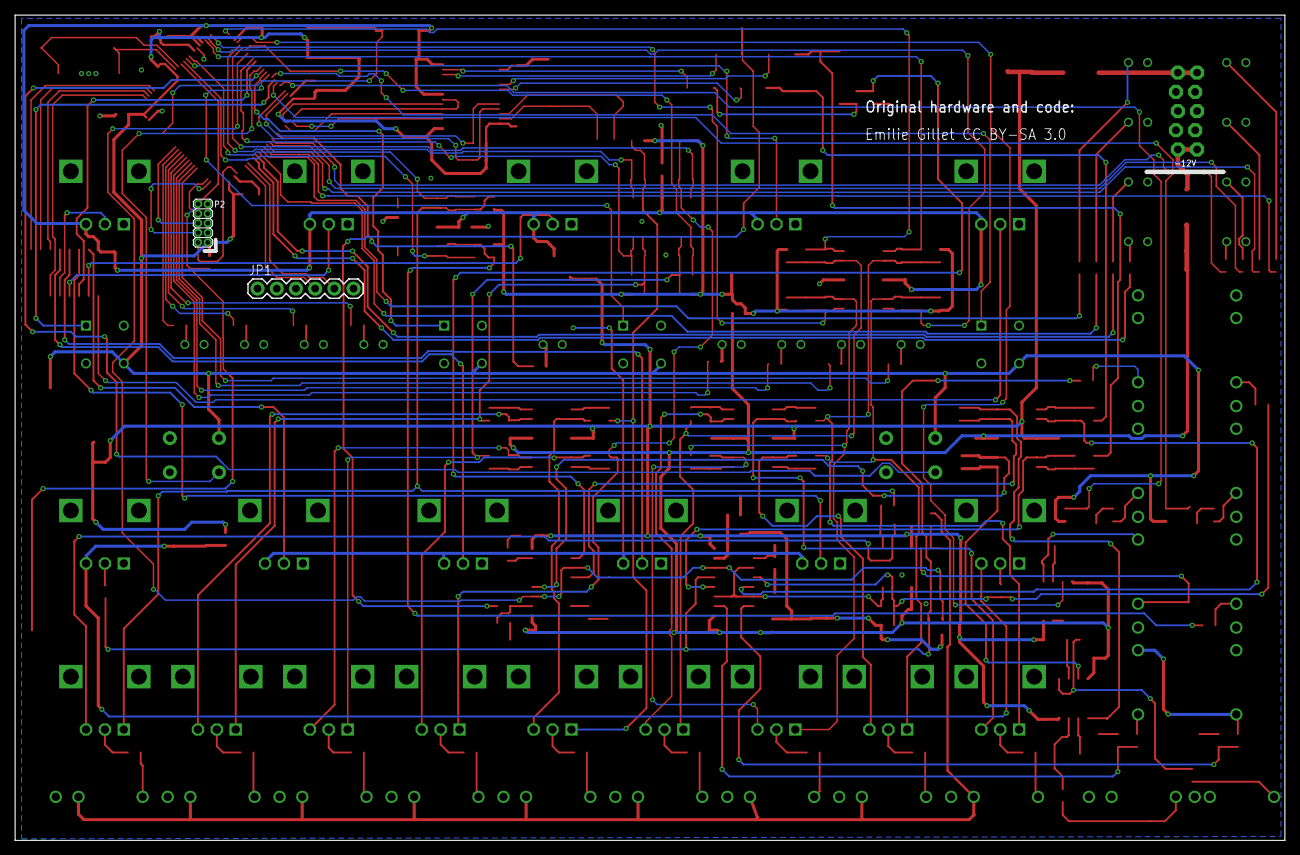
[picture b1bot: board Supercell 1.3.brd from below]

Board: 2 copper layers, 168.0 x 109.2 mm, 293 parts (2 on the bottom side), 205 nets.

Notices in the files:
Microcell/hardware/Microcell 1.4.brd:
Emilie Gillet CC BY-SA 3.0
